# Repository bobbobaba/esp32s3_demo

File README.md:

# ESP32-S3 AI Watch UI

这是一个基于 ESP32-S3 N16R8 的小屏 AI 终端固件项目，使用 128x128 ST7735 屏幕、四个按键、I2S 麦克风、MAX98357A 喇叭、MPU6050 传感器和板载 RGB LED。

项目当前仍处于快速迭代阶段：核心功能已经可用，UI 还在从手写绘制逐步迁移到 LVGL/EEZ Studio 的可视化设计流程。

## 功能概览

- 128x128 ST7735 表盘首页
- 四按键菜单系统
- 手机扫码 Wi-Fi 配网页
- 天气/服务器状态展示接口
- AI 语音通话模式
  - 自动监听
  - 检测停顿后自动提交
  - 播放 AI 回复
  - 播放完成后自动继续监听
- I2S 麦克风录音
- MAX98357A I2S 喇叭播放
- 板载 RGB LED 控制和特效
- MPU6050 传感器页面
  - 原始加速度/陀螺仪/温度
  - 姿态角
  - 水平仪
  - 步数/估算里程
  - 摇动、抬手、静止、疑似跌落/撞击事件
  - 零位校准
- UI 页面关系蓝图：`docs/ui-flow.md`

## 最新更新

- 完整更新记录见：[CHANGELOG.md](CHANGELOG.md)
- 最新一次更新：新增 EEZ Studio 128x128 可视化 UI 草图，预建首页、菜单、AI 通话、设置、服务器、LED、Wi-Fi 配网和 MPU 数据页面。
- UI 迁移进度：已完成 `UiPage` 状态机、`dispatchButton()` 按键调度和 EEZ 项目骨架，下一步是把 EEZ 导出页面接入固件渲染流程。

## 当前功能更新摘要

- 新增 AI 半双工通话模式：`P7 CALL` 开始，`P4` 退出。
- AI 通话不再需要每轮手动停止，检测到说话停顿后自动提交。
- MPU 页面改为局部刷新，避免整屏闪烁导致文字看不清。
- MPU 断线时不会卡死页面，SDA/SCL 异常会显示 `MPU6050 OFF`，并保持按键可退出。
- MPU 事件触发 LED 改为可配置，默认关闭；在 `EVENT` 页面用 `P6` 切换。
- 增加 Wi-Fi 设置二维码页面，手机可查看网络状态并重新配网。
- 新增 `docs/ui-flow.md`，用于后续迁移到 EEZ Studio/EEZ Flow。
- 公开仓库版本已脱敏：不包含真实服务器地址、Wi-Fi 密码、服务账号密码、token 或私钥。

## 快速开始

1. 安装 PlatformIO。
2. 按 [docs/hardware-wiring.md](docs/hardware-wiring.md) 完成接线。
3. 编译固件：

```bash
pio run
```

4. 连接 ESP32-S3 串口并烧录：

```bash
pio run --target upload --upload-port /dev/ttyACM0
```

5. 首次启动后连接 `ESP32S3-Setup` 热点，手机打开 `http://192.168.4.1/` 配网。

## 项目框架

```text
esp32s3_wifi_setup/
├── boards/
│   └── esp32-s3-n16r8-qspi.json      # 自定义 ESP32-S3 N16R8 QSPI 板卡配置
├── docs/
│   ├── eez-studio.md                 # EEZ Studio/LVGL 接入计划
│   ├── hardware-wiring.md            # 硬件接线说明
│   ├── ota-api.md                    # OTA 接口设计
│   └── ui-flow.md                    # 页面/按钮/状态机蓝图
├── eez-ui/
│   └── esp32s3_wifi_setup/           # EEZ Studio 128x128 UI 草图工程
├── src/
│   ├── main.cpp                      # 主固件逻辑
│   ├── lv_conf.h                     # LVGL 配置
│   ├── mi_style_watchface.h          # 表盘资源
│   ├── mi_style_watchface_preview.png
│   ├── radar_watchface.h             # 表盘资源
│   └── OPEN_SOURCE_UI_NOTICE.md      # 开源 UI 资源说明
├── platformio.ini                    # PlatformIO 工程配置
├── .gitignore
└── README.md
```

## 软件架构

当前 `main.cpp` 里主要包含这些模块：

- 硬件初始化
  - ST7735 SPI 屏幕
  - LVGL 显示缓冲
  - 四个按键
  - RGB LED
  - MPU6050 I2C
  - I2S 麦克风/喇叭
- 网络配置
  - ESP32 AP 配网热点
  - Web 配网页
  - DNS captive portal
- 数据服务
  - 登录服务接口
  - 天气接口
  - 服务器状态接口
  - AI 语音接口
- UI 页面
  - 首页
  - 菜单
  - 设置
  - Wi-Fi 配网
  - 服务器状态
  - LED 控制
  - AI 通话
  - MPU 数据/姿态/水平仪/里程/事件
- 后台任务
  - 天气刷新
  - 服务器状态刷新
  - OTA 更新检查
  - 语音录音/上传/播放
  - MPU 手势/事件检测
  - LED 特效

当前页面状态已经收口为单一 `UiPage` 状态机，后续会继续把按键分发和页面渲染迁移到 LVGL/EEZ Studio 生成的页面代码。

## 硬件接线

### ST7735 128x128 屏幕

| 屏幕引脚 | ESP32-S3 |
| --- | --- |
| LED | GPIO15 |
| SCL/SCK | GPIO12 |
| SDA/MOSI | GPIO11 |
| DC/RS | GPIO9 |
| CS | GPIO10 |
| RST | GPIO8 |
| VCC | 3.3V |
| GND | GND |

### 四个按键

按键为低电平触发，固件使用内部上拉。

| 按键 | ESP32-S3 |
| --- | --- |
| P4 | GPIO4 |
| P5 | GPIO5 |
| P6 | GPIO6 |
| P7 | GPIO7 |

### I2S 麦克风

| 麦克风信号 | ESP32-S3 |
| --- | --- |
| BCLK | GPIO16 |
| WS/LRCLK | GPIO17 |
| SD/DOUT | GPIO18 |
| VCC | 3.3V |
| GND | GND |

### MAX98357A 喇叭功放

| MAX98357A | ESP32-S3 |
| --- | --- |
| BCLK | GPIO16 |
| LRC/WS | GPIO17 |
| DIN | GPIO14 |
| VIN | 3.3V 或 5V，按模块规格选择 |
| GND | GND |

### MPU6050

| MPU6050 | ESP32-S3 |
| --- | --- |
| VCC | 3.3V |
| GND | GND |
| SCL | GPIO41 |
| SDA | GPIO42 |
| INT | 可选 GPIO13 |
| XDA | 不接 |
| XCL | 不接 |
| ADC | 不接 |

## 按键操作

### 全局

| 按键 | 作用 |
| --- | --- |
| P4 | 返回/退出当前页面 |
| P5 | 上一个/减小/清零，取决于页面 |
| P6 | 下一个/增加/切换，取决于页面 |
| P7 | 确认/开始/校准，取决于页面 |

### 菜单页

| 按键 | 作用 |
| --- | --- |
| P4 | 返回首页 |
| P5 | 上一个菜单项 |
| P6 | 下一个菜单项 |
| P7 | 打开当前菜单项 |

### AI 通话页

| 按键 | 作用 |
| --- | --- |
| P4 | 退出通话 |
| P5 | 音量减 |
| P6 | 音量加 |
| P7 | 开始通话 |

### MPU 页面

| 页面 | 按键 | 作用 |
| --- | --- | --- |
| MPU DATA / ANGLE / LEVEL / ODO / EVENT | P7 | 零位校准 |
| ODO | P5 | 清步数 |
| EVENT | P5 | 清事件计数 |
| EVENT | P6 | 开关 MPU 事件 LED 反馈 |

## 构建

安装 PlatformIO 后执行：

```bash
pio run
```

烧录：

```bash
pio run --target upload --upload-port /dev/ttyACM0
```

如果串口不同，先查看设备：

```bash
pio device list
```

## 私有配置和脱敏说明

公开仓库不包含真实服务器地址、Wi-Fi 密码、服务账号密码、token 或私钥。

固件中的服务地址通过编译宏配置：

```cpp
#ifndef SERVICE_BASE_URL
#define SERVICE_BASE_URL "http://example.invalid"
#endif
```

本地使用时可以在私有且被忽略的 PlatformIO 配置中加入：

```ini
build_flags =
    -DSERVICE_BASE_URL=\"http://example.invalid/base-path\"
```

也可以按需添加：

```ini
build_flags =
    -DPROVISION_SSID=\"your_wifi\"
    -DPROVISION_PASSWORD=\"replace_me\"
    -DPROVISION_SERVICE_USER=\"your_user\"
    -DPROVISION_SERVICE_PASSWORD=\"replace_me\"
    -DSERVICE_BASE_URL=\"http://example.invalid/base-path\"
```

不要把真实值提交到 Git。

已忽略的敏感/本地文件包括：

- `.env`
- `.env.*`
- `*.pem`
- `*.key`
- `secrets.*`
- `credentials.*`
- `platformio_override.ini`
- `local_*.ini`
- `.pio/`

## UI 迁移计划

当前 UI 由手写 ST7735 绘制和部分 LVGL 组成。后续计划：

1. 已完成：用 `UiPage` 状态机替换多个 `showXxxPage` 布尔变量。
2. 已完成：把按键统一成 `dispatchButton()`。
3. 进行中：把每个页面拆成静态布局和动态数据刷新；AI 通话页、菜单页、设置页、服务器页、LED 页、Wi-Fi 页已拆分或缓存，MPU 页面已有动态刷新基础。
4. 使用 EEZ Studio/EEZ Flow 重新设计界面和页面跳转关系。
5. 导出 LVGL 页面代码，逐步替换手写 UI。

页面关系图和迁移蓝图见：

[docs/ui-flow.md](docs/ui-flow.md)

EEZ Studio 接入说明见：

[docs/eez-studio.md](docs/eez-studio.md)

OTA 接口设计见：

[docs/ota-api.md](docs/ota-api.md)

## 许可和资源说明

项目代码准备作为开源固件发布。部分 UI 资源来源说明见：

[src/OPEN_SOURCE_UI_NOTICE.md](src/OPEN_SOURCE_UI_NOTICE.md)

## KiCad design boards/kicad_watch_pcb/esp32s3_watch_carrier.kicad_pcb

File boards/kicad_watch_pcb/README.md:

# ESP32-S3 AI Watch Carrier PCB

这是当前 `esp32s3_wifi_setup` 固件对应的 KiCad 转接底板初版。

## 文件

- `esp32s3_watch_carrier.kicad_pro`: KiCad 9 项目文件
- `esp32s3_watch_carrier.kicad_pcb`: PCB 板文件
- `open_kicad_watch.sh`: 兼容启动脚本，强制使用 Mesa 软件 OpenGL，避免部分 NVIDIA GLX 环境下 PCB 编辑器闪退

## 当前设计范围

- ESP32-S3 开发板接口 `J1` 已从单列 GPIO 总线改为 A1 双排 2.54mm 插座占位，带开发板外形框、右排丝印参考孔和 USB 方向丝印。
- `J1` 左排保留当前已布通的固件 GPIO 网络；右排当前只是丝印预览，不生成铜焊盘，等实测 ESP32-S3-N16R8 开发板脚位后再改成真实双排母座。
- ST7735 屏幕、I2S 麦克风、MAX98357A、MPU6050 以模块排针连接。
- P4/P5/P6/P7 四个按键已放置为板载轻触按键，低电平触发，另一端接 GND。
- J2/J3/J4/J5 外设电源脚旁已放置本地去耦电容，J6 电源入口已放置 bulk 电容位。
- 板框为 180mm x 120mm 的草图尺寸，便于先看布局和连线关系。

## ESP32-S3 开发板插座说明

当前 `J1` 不是最终可直接制板的精确开发板封装，而是为了在 KiCad 里看清“开发板双排插入”的 A1 占位封装：

- 孔距按常见 2.54mm 排针处理，双排中心距暂按 25.4mm。
- 丝印中的 `USB` 标识表示开发板 USB 口朝向。
- 左排当前承担所有已验证固件网络，右排仅用于外形预览，避免在没有实物脚位时误连或让既有走线穿过真实焊盘。
- 制板前必须拿卡尺确认开发板两排排针中心距、每排孔数、USB 方向和每个 GPIO 的真实位置，再把右排也按真实 pinout 接入。

如果直接拿当前 A1 占位去打板，只能用于结构/走线验证，不能保证你的 ESP32-S3-N16R8 开发板插上后每个 GPIO 都对。

## 固件 GPIO 映射

| 功能 | GPIO |
| --- | --- |
| TFT LED | GPIO15 |
| TFT SCK | GPIO12 |
| TFT MOSI | GPIO11 |
| TFT DC | GPIO9 |
| TFT CS | GPIO10 |
| TFT RST | GPIO8 |
| P4/P5/P6/P7 | GPIO4/GPIO5/GPIO6/GPIO7 |
| I2S BCLK | GPIO16 |
| I2S WS | GPIO17 |
| I2S MIC SD | GPIO18 |
| I2S SPK DIN | GPIO14 |
| MPU SCL/SDA | GPIO41/GPIO42 |
| MPU INT | GPIO13 |

## 当前 PCB 约束

- 当前 A0 版本是可焊接验证底板，不是最终手表小尺寸压缩板。
- MAX98357A `VIN` 已接 `5V`，用于提高喇叭输出功率。
- MPU6050 I2C 使用当前固件定义的 `GPIO41=SCL`、`GPIO42=SDA`，不是 P7/P8。
- J1 右排当前只是丝印参考孔，不参与板上网络；电源母线从 J1 左排下方 GND/3V3/5V 引出。
- 已通过 KiCad DRC：0 条违规、0 个未连接项。

## 已落实的布线优化

- 5V、3V3、GND 使用加粗走线，普通信号线使用 0.25mm。
- I2S 麦克风和 MAX98357A 共用 BCLK/WS，SD 与 DIN 分开走线。
- ST7735、I2S、MPU6050、按键网络全部布通，未连接提示线清零。
- C1-C4 为外设 100nF 去耦电容位，分别靠近 J2/J3/J4/J5；C5 为 J6 输入 bulk 电容位。

## A1 制版前建议

- 按最终手表外壳尺寸重新压缩板框和器件坐标。
- 将 C1-C5 按装配能力选择 0402/0603/0805；当前 A0 偏向手工焊接友好。
- J6 电源入口增加防反接二极管、0805 自恢复保险丝和 TVS/ESD 保护。
- 屏幕、音频、I2C 外接排线信号预留 0603 串阻位。
- 若追求更低噪声，重排为屏幕区、音频区、传感器区、按键/电源区，并减少 I2S/SPI 高速线过孔。

## 后续需要确认

- ESP32-S3 开发板实际引脚排布、两排中心距、每排孔数、USB 方向。
- 屏幕、麦克风、MAX98357A、MPU6050 模块的实际排针方向。
- 最终手表外壳尺寸、安装孔位置、电池/充电模块位置。

## 打开方式

如果直接打开 KiCad/PCB Editor 闪退，使用：

```bash
./open_kicad_watch.sh
```

本机实测闪退点在 `libGLX_nvidia.so.0` 创建 OpenGL 上下文，脚本已设置 `__GLX_VENDOR_LIBRARY_NAME=mesa` 和 `MESA_LOADER_DRIVER_OVERRIDE=llvmpipe` 避开该问题。

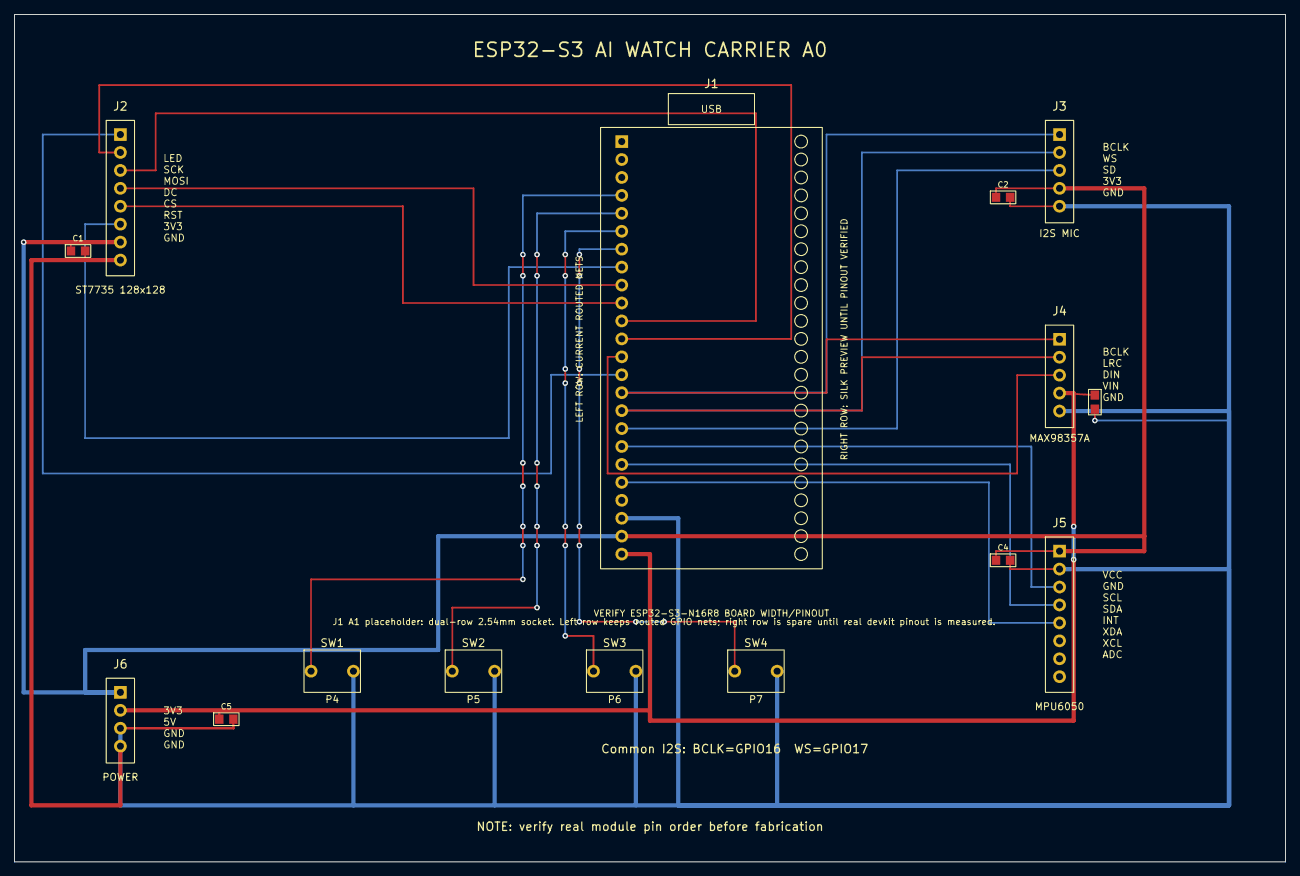
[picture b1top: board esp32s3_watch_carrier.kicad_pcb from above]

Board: 2 copper layers, 180.0 x 120.0 mm, 15 parts (0 on the bottom side), 20 nets.

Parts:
C1: 100nF TFT; C_0805_WATCH
C2: 100nF MIC; C_0805_WATCH
C3: 100nF AMP; C_0805_WATCH
C4: 100nF MPU; C_0805_WATCH
C5: 10uF IN; C_0805_WATCH
J1: ESP32-S3 DEVKIT SOCKET A1 PLACEHOLDER; ESP32S3_DEVKIT_SOCKET_A1_PLACEHOLDER
J2: ST7735 128x128; TFT_ST7735_HEADER
J3: I2S MIC; I2S_MIC_HEADER
J4: MAX98357A; MAX98357A_HEADER
J5: MPU6050; MPU6050_HEADER
J6: POWER; POWER_HEADER
SW1: P4; SW_P4
SW2: P5; SW_P5
SW3: P6; SW_P6
SW4: P7; SW_P7

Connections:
3V3: C1.1, C2.1, C4.1, J1.23, J2.7, J3.4, J5.1, J6.1
5V: C3.1, C5.1, J1.24, J4.4, J6.2
GND: C1.2, C2.2, C3.2, C4.2, C5.2, J1.22, J2.8, J3.5, J4.5, J5.2, J6.3, J6.4, SW1.2, SW2.2, SW3.2, SW4.2
GPIO4_P4: J1.4, SW1.1
GPIO5_P5: J1.5, SW2.1
GPIO6_P6: J1.6, SW3.1
GPIO7_P7: J1.7, SW4.1
GPIO8_TFT_RST: J1.8, J2.6
GPIO9_TFT_DC: J1.9, J2.4
GPIO10_TFT_CS: J1.10, J2.5
GPIO11_TFT_MOSI: J1.11, J2.3
GPIO12_TFT_SCK: J1.12, J2.2
GPIO13_MPU_INT: J1.20, J5.5
GPIO14_SPK_DIN: J1.13, J4.3
GPIO15_TFT_LED: J1.14, J2.1
GPIO16_I2S_BCLK: J1.15, J3.1, J4.1
GPIO17_I2S_WS: J1.16, J3.2, J4.2
GPIO18_MIC_SD: J1.17, J3.3
GPIO41_MPU_SCL: J1.18, J5.3
GPIO42_MPU_SDA: J1.19, J5.4
